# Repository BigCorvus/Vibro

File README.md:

# Vibro
Carrier board for 4x10mm vibration motors and the necessary circuitry. You can choose between mosfet and BJT as a switch.

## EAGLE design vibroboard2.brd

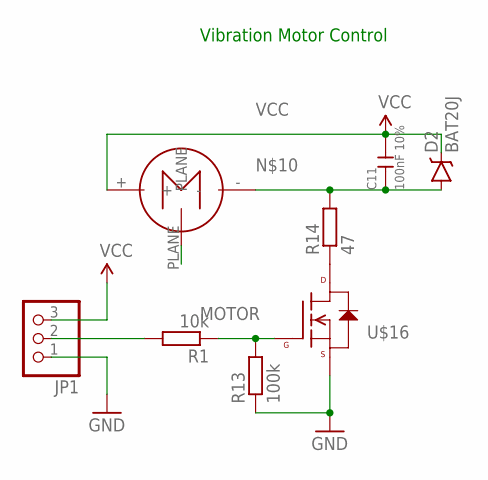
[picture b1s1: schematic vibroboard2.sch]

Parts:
C11: 100nF 10%; C0603
D2: BAT20J; SOD-323
JP1: PINHD-1X3; 1X03
R1: 10k; R0603
R13: 100k; R0603
R14: 47; R0603
U$16: N-CHANNEL-MOSFET-BSS138; SOT23-3
U$23: VIBRO

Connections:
GND: JP1.1, R13.1, U$16.2 (S)
MOTOR: R1.1, R13.2, U$16.1 (G)
unnamed: JP1.2, R1.2
unnamed: R14.1, U$16.3 (D)
unnamed: C11.1, D2.A, R14.2, U$23.-
PLANE: U$23.PLANE
VCC: C11.2, D2.C, JP1.3, U$23.+

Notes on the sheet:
Vibration Motor Control

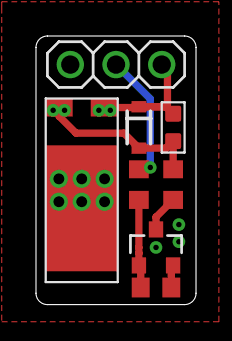
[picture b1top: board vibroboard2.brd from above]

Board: 2 copper layers, 8.9 x 14.9 mm, 8 parts (0 on the bottom side), 6 nets.

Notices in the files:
parts and their libraries:
SparkFun-DiscreteSemi: Licensing: Creative Commons ShareAlike 4.0 International - https://creativecommons.org/licenses/by-sa/4.0
